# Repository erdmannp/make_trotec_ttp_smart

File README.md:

# Trotec TTP5 Dehumidifier

I bought a used Troted TTP5, which is a peltier based dehumidifier. It is absolutely sufficient for small rooms like my bathroom. But it only has two modes: On and Off. The original PCB looks like this:

The 9 Volt input power is connected to the "DC-12" port. Peltier and Fan are connected in the left of this image. The connector on the right is the "water level high" switch. In this model it is literally a switch which is turned on by a high water level. 

My idea is to take the "water level high" signal input and "reuse" it as the enable or disable of the dehumidifier. So when turned on the dehumidifier will no longer be on, it will only be used if the humidity sensor shows a value below the threshold. 
The TTP5 PCB will act like the watertank is full, in case of low humidity or watertank full.

I designed the PCB in a way that it is piggybacked by the normal PCB:

The "water level high" signal is now handled by the added PCB.

After a testphase I connected the humidity sensor inside of the TTP5 chassis. 

The configuration Webinterface is very rudimental, but it does the job.

# To Do's

- Display the waterlevel status on webpage.
- Display the current status (peltier and fan On or Off).
- Add MQTT protocol and support.
- Add a small pump and connect it to the sewer pipe.

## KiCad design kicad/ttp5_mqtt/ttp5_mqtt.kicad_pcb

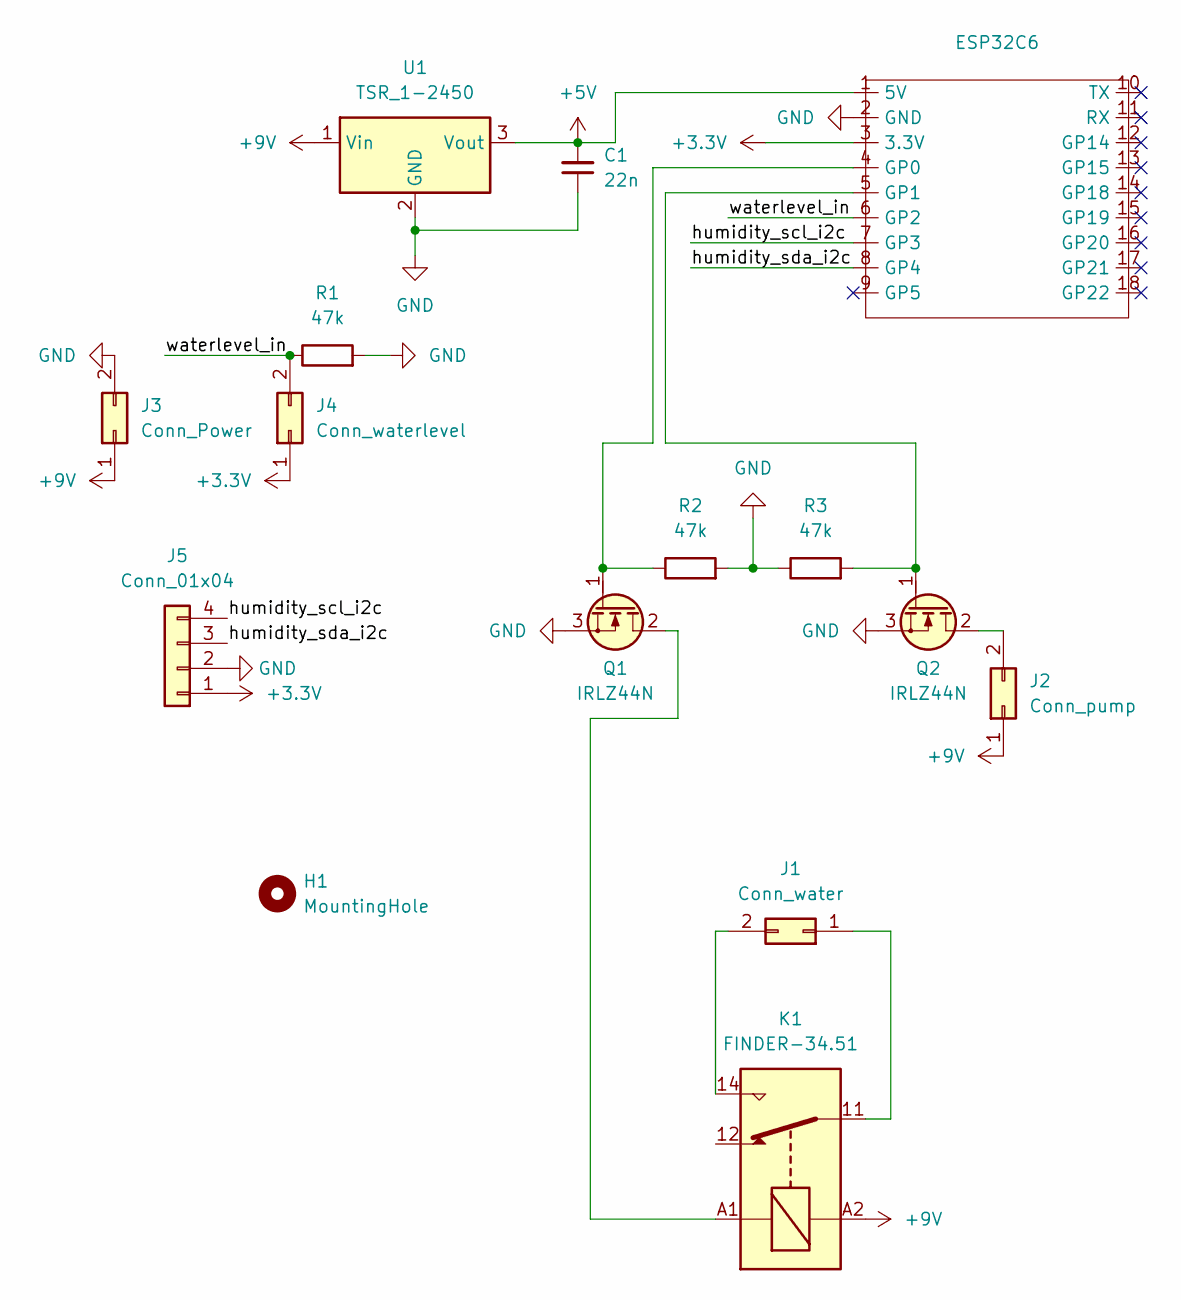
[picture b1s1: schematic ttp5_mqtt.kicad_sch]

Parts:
C1: 22n; R_0603_1608Metric_Pad0.98x0.95mm_HandSolder
ESP32C6: Waveshare ESP32-C6 Mini Development Board
H1: MountingHole; MountingHole_6.5mm
J1: Conn_water; PinHeader_2x01_P2.54mm_Vertical
J2: Conn_pump; PinHeader_2x01_P2.54mm_Vertical
J3: Conn_Power; Molex_KK-396_A-41791-0002_1x02_P3.96mm_Vertical
J4: Conn_waterlevel; PinHeader_2x01_P2.54mm_Vertical
J5: Conn_01x04; PinHeader_1x04_P2.54mm_Vertical
K1: FINDER-34.51; Relay_SPDT_Finder_34.51_Vertical
Q1, Q2: IRLZ44N; TO-220-3_Vertical_GDS
R1, R2, R3: 47k; R_0201_0603Metric_Pad0.64x0.40mm_HandSolder
U1: TSR_1-2450; Converter_DCDC_TRACO_TSR-1_THT

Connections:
+3.3V: ESP32C6.3 (3.3V), J4.1, J5.1
+5V: C1.2, ESP32C6.1 (5V), U1.3 (Vout)
+9V: J2.1, J3.1, K1.A2, U1.1 (Vin)
/humidity_scl_i2c: ESP32C6.7 (GP3), J5.4
/humidity_sda_i2c: ESP32C6.8 (GP4), J5.3
/waterlevel_in: ESP32C6.6 (GP2), J4.2, R1.1
GND: C1.1, ESP32C6.2 (GND), J3.2, J5.2, Q1.3 (S), Q2.3 (S), R1.2, R2.2, R3.1, U1.2 (GND)
unnamed: ESP32C6.4 (GP0), Q1.1 (G), R2.1
unnamed: ESP32C6.5 (GP1), Q2.1 (G), R3.2
unnamed: J1.1, K1.11
unnamed: J1.2, K1.14
unnamed: J2.2, Q2.2 (D)
unnamed: K1.A1, Q1.2 (D)

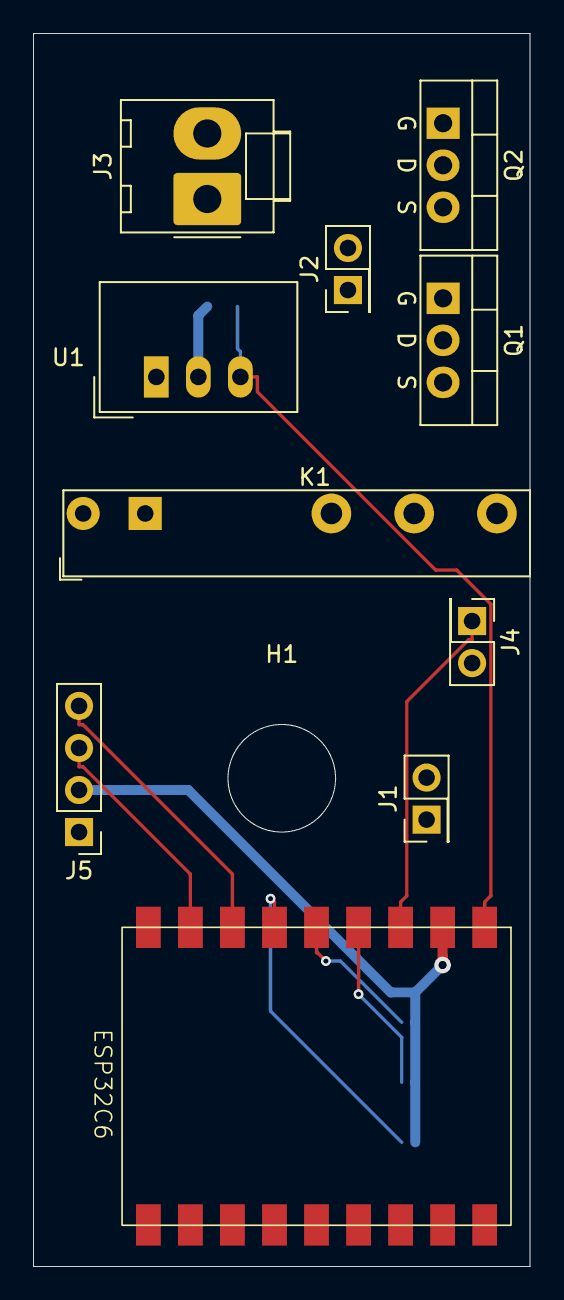
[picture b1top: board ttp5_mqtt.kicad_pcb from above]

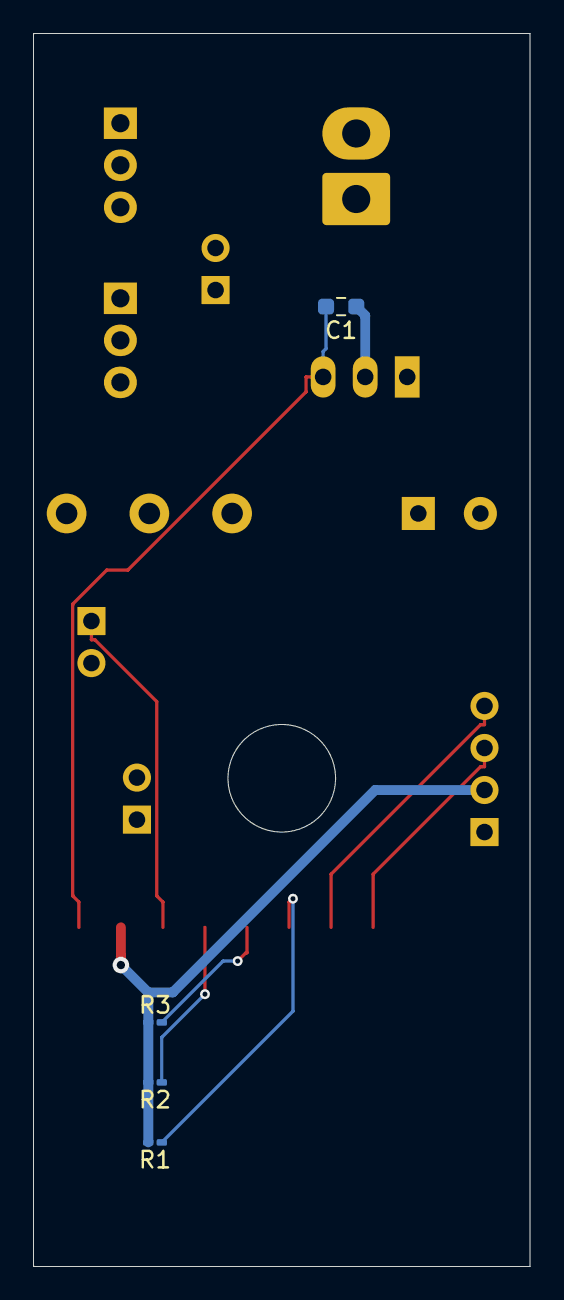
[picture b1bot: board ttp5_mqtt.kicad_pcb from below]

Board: 4 copper layers, 30.0 x 74.5 mm, 15 parts (4 on the bottom side), 13 nets.

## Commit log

2024-12-24 Add kicad files
2024-12-27 add sources
2025-01-11 Add configuration files and SHTC3 i2c reader
2025-01-26 Add initial documentation
